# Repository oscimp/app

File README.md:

# app
OscillatorIMP ecosystem Linux applications

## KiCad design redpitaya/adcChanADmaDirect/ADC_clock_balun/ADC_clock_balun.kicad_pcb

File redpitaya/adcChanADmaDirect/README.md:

# Adc ChanA to CPU with DMA direct

## Purpose

This application is used to fetch, from ADC channelA, a large amount of sample.
By using the DMA to store data in CPU RAM instead of BRAM it's possible to
bypass the redpitaya Zynq resources limitation.

By default this project fetches 1Msamples 16bits at full speed (125MS/s)

To sample both ADC (instead of only ADC channelA), update the design with
```
NB_INPUT 2
```
The number of samples and connections will be updated automagically.

## Usage

After executing *adcChanADmaDirect_us* a binary file called *dump.bin* is
present in current directory. To read content using Gnu Octave in single channel mode:
```
fd = fopen("dump.bin"); dd = fread(fd, inf, "int16"); fclose(fd); 
```
and in dual channel mode
```
fd = fopen("dump.bin"); dd = fread(fd, inf, "int16"); fclose(fd); d1=dd(1:2:end); d2=dd(2:2:end);
```

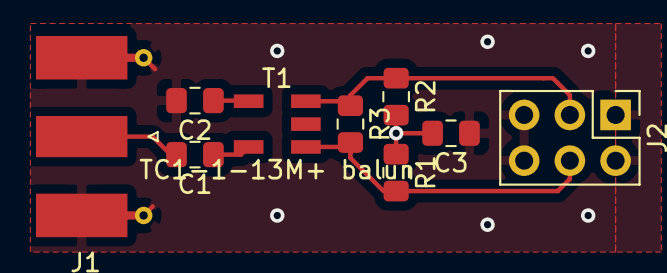
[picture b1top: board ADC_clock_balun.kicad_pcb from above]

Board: 2 copper layers, 9 parts (0 on the bottom side), 7 nets.

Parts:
C1, C2, C3: 100n; C_0805_2012Metric_Pad1.15x1.40mm_HandSolder
J1: Conn_Coaxial; SMA_Molex_73251-1153_EdgeMount_Horizontal
J2: Conn_02x03_Counter_Clockwise; PinHeader_2x03_P2.54mm_Vertical
R1, R2: 50; R_0805_2012Metric_Pad1.15x1.40mm_HandSolder
R3: 100; R_0805_2012Metric_Pad1.15x1.40mm_HandSolder
T1: TC1-1-13M+ balun; AT224-1A

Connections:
GND: C2.2, C3.1, J1.2, J2.1, J2.2, J2.5, J2.6
unnamed: C1.1, T1.4
unnamed: C1.2, J1.1
unnamed: C2.1, T1.6
unnamed: C3.2, R1.1, R2.2
unnamed: J2.3, R2.1, R3.1, T1.1
unnamed: J2.4, R1.2, R3.2, T1.3

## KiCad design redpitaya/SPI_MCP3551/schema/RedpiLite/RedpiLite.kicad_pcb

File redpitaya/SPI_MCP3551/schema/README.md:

Eagle 7 CAD electronics board schematic and layout, imported into KiCAD 7
and assigned layers (top, bottom and dimensions to F.Cu, B.Cu and Edge Cuts).

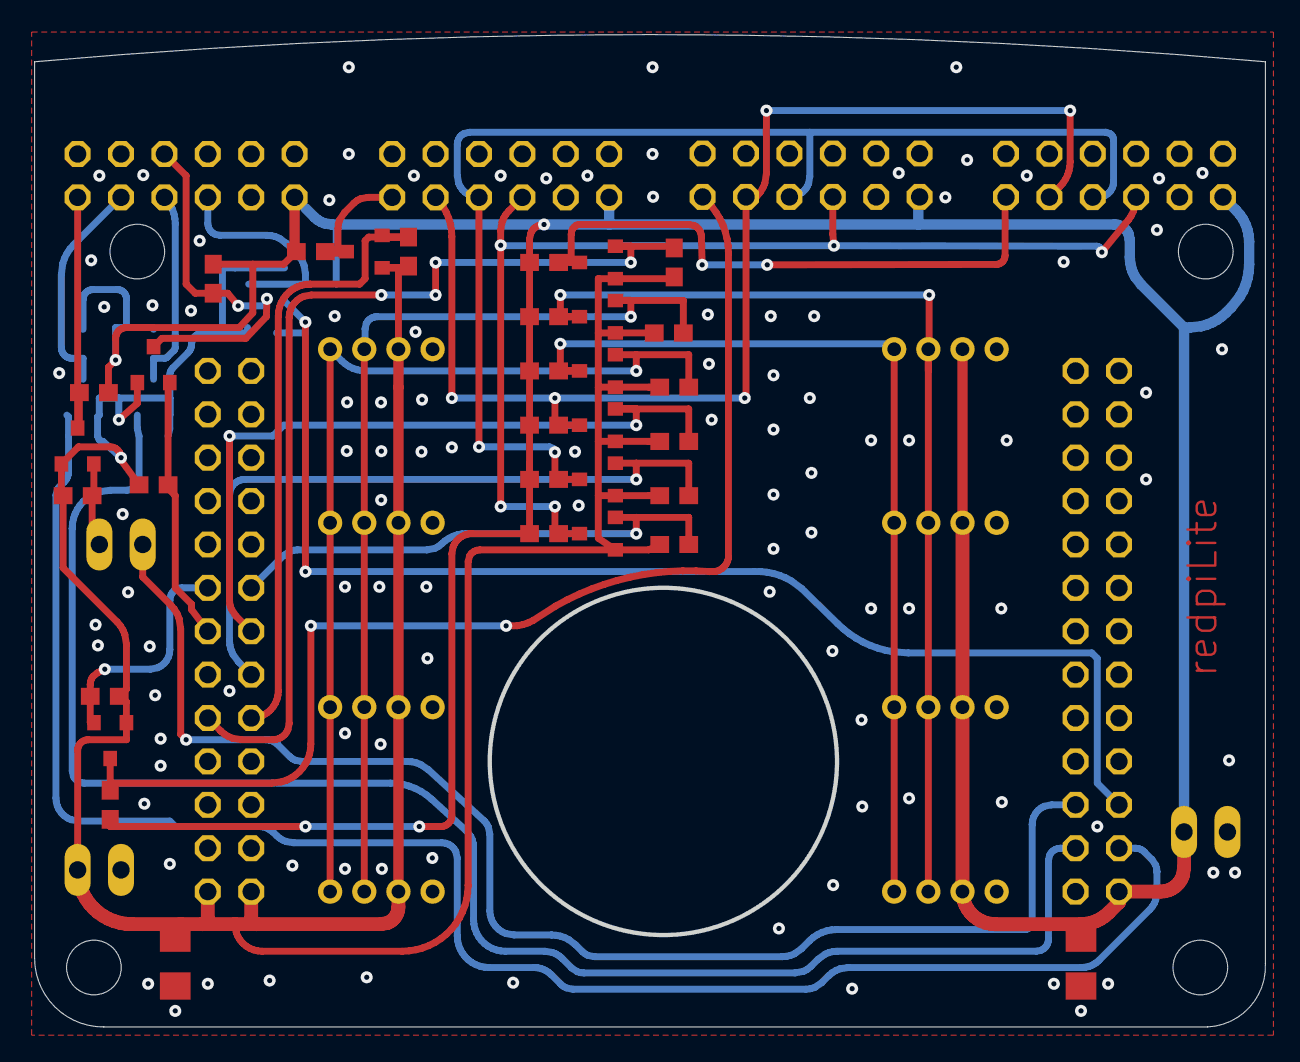
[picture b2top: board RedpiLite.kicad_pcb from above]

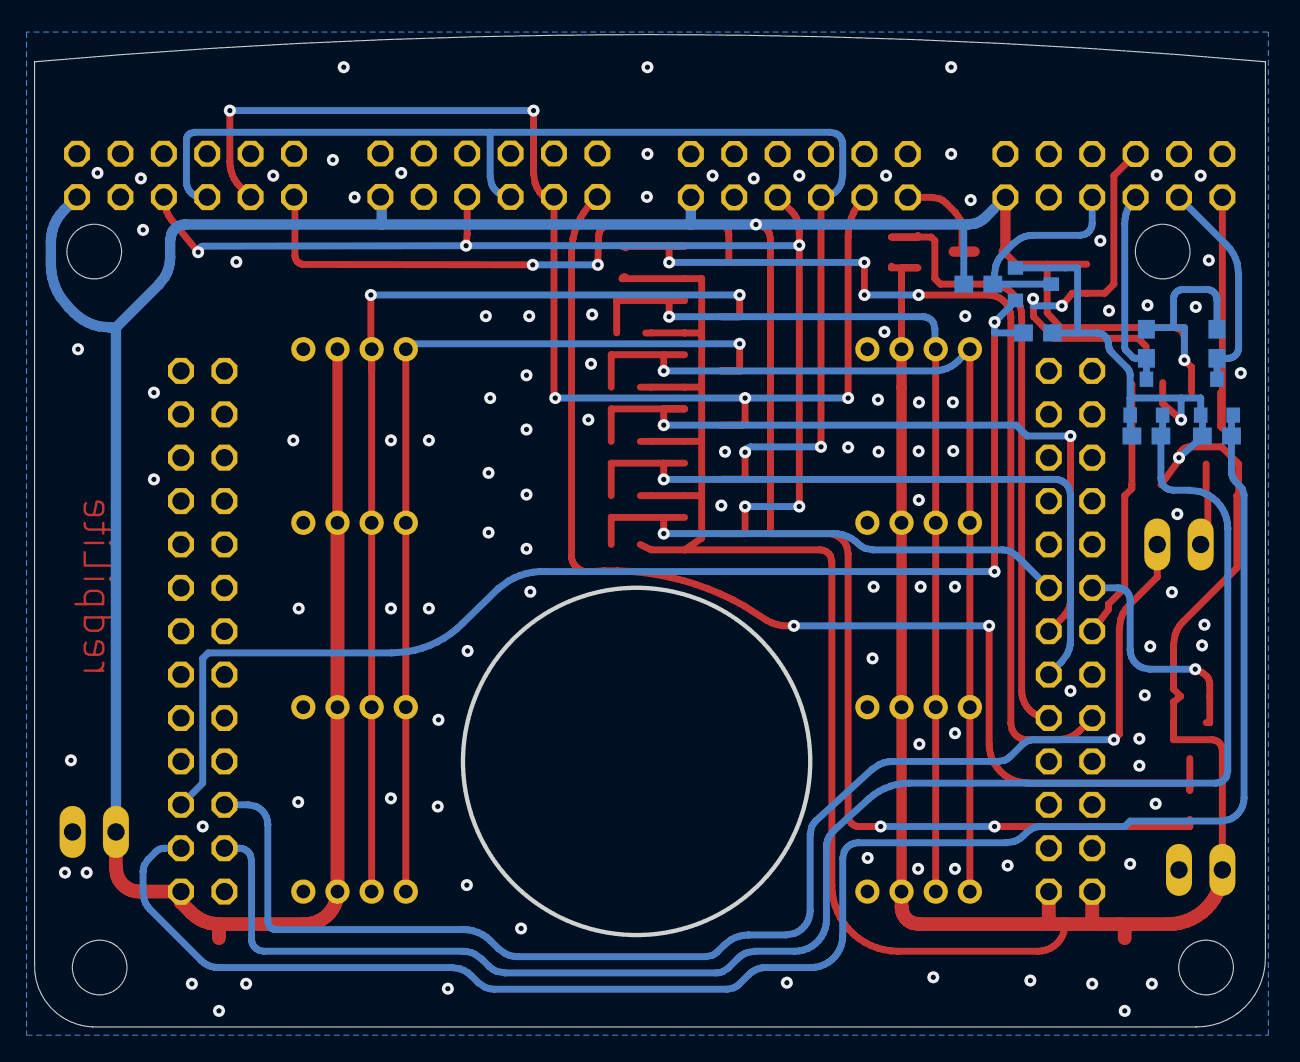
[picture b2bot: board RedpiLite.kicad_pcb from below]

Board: 2 copper layers, 71.8 x 57.9 mm, 62 parts (9 on the bottom side), 30 nets.

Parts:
+5V0: 1X02
@HOLE0, @HOLE1, @HOLE2, @HOLE3: (no value)
C1, C2: 4.7µF; C1206
E1, E2: 2X13
JUMP0: 1X02
P1, P2, P3, P4, P5, P6, P7, P8: JST-PH4
PMOD1, PMOD2, PMOD3, PMOD4: 2X06_90
R1, R2, R3, R4, R5, R6, R7, R8, R9, R10, R11, R12, R13, R14, R15, R16, R17, R18, R19, R20, R21, R22, R23, R24, R25, R26: 10K; 0603-RES
T1, T2, T3, T4, T5, T6, T7, T8, T9, T10, T11, T12, T13: BSS138; SOT23-3
UNK3V3: 1X02

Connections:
+3V3: C2.1, E1.1, E1.2, P1.3, P2.3, P3.3, P4.3, R1.1, R3.1, R5.1, R7.1, R9.1, R11.1, R13.1, R15.1, R17.1, R19.1, R21.1, R23.1, R25.1, T1.1, T2.1, T3.1, T4.1, T5.1, T6.1, T7.1, T8.1, T9.1, T10.1, T11.1, T12.1, T13.1, UNK3V3.1
+5V: +5V0.1, C1.1, E2.1, P5.3, P6.3, P7.3, P8.3, PMOD1.11, PMOD2.11, PMOD3.11, PMOD4.11, R2.1, R4.1, R6.1, R8.1, R10.1, R12.1, R14.1, R16.1, R18.1, R20.1, R22.1, R24.1, R26.1
CLK1: PMOD4.7, R20.2, T10.3
CLK2: PMOD1.7, PMOD2.7, PMOD3.7, R2.2, T1.3
CS1: PMOD1.1, R12.2, T6.3
CS2: PMOD2.1, R14.2, T7.3
CS3: PMOD3.1, R16.2, T8.3
CS4: PMOD4.1, R18.2, T9.3
CS#: E2.6, JUMP0.1
CS#': JUMP0.2, R17.2, T9.2
GND: +5V0.2, C1.2, C2.2, E1.19, E1.20, E1.25, E1.26, E2.12, E2.21, E2.22, E2.25, E2.26, P1.4, P2.4, P3.4, P4.4, P5.4, P6.4, P7.4, P8.4, PMOD1.9, PMOD2.9, PMOD3.9, PMOD4.9, UNK3V3.2
MISO: E2.4, R21.2, T11.2
MISO1: PMOD4.5, R22.2, T11.3
MISO2: PMOD1.5, PMOD2.5, PMOD3.5, R4.2, T2.3
MOSI: E2.3, R23.2, T12.2
MOSI1: PMOD4.3, R24.2, T12.3
MOSI2: PMOD1.3, PMOD2.3, PMOD3.3, R6.2, T3.3
PL_DIO3_N_CS1: E1.10, R11.2, T6.2
PL_DIO3_P_CS3: E1.9, R15.2, T8.2
PL_DIO4_P-MISO: E1.11, R3.2, T2.2
PL_DIO5_P-MOSI: E1.13, R5.2, T3.2
PL_DIO6_N_CS2: E1.16, R13.2, T7.2
PL_DIO6_P-CLK: E1.15, R1.2, T1.2
SCK: E2.5, R19.2, T10.2
SCL: P1.1, P2.1, P3.1, P4.1, R7.2, T4.2
SCL_5V: P5.1, P6.1, P7.1, P8.1, R8.2, T4.3
SDA: P1.2, P2.2, P3.2, P4.2, R9.2, T5.2
SDA_5V: P5.2, P6.2, P7.2, P8.2, R10.2, T5.3
SDSYNC: PMOD4.6, R26.2, T13.3
TEC_ON/OFF: E1.14, R25.2, T13.2

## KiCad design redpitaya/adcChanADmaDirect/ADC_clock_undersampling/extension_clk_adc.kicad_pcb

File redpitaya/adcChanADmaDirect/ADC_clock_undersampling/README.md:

Hardware modifications of the 14-bit Red Pitaya (also known as STEMlab 125-14) described
in report.pdf, and the associated KiCAD files (courtesy of Gilles Martin, FEMTO-ST, France)
for undersampling by getting rid of the unbalanced-balanced amplifier also acting as
low pass filter. Replacing the active amplifier with a broadband balun (tested over the
whole track-and-hold range up to 875 MHz input frequency) requires soldering three tiny
wires (differential pair + Vref) on each channel at your own risks after removing the
inductors connecting the differential amplifier output to the ADC inputs. The Vref signal
trace must be cut before soldering a wire to the via pad whose varnish will have been
removed with a sharp blade.

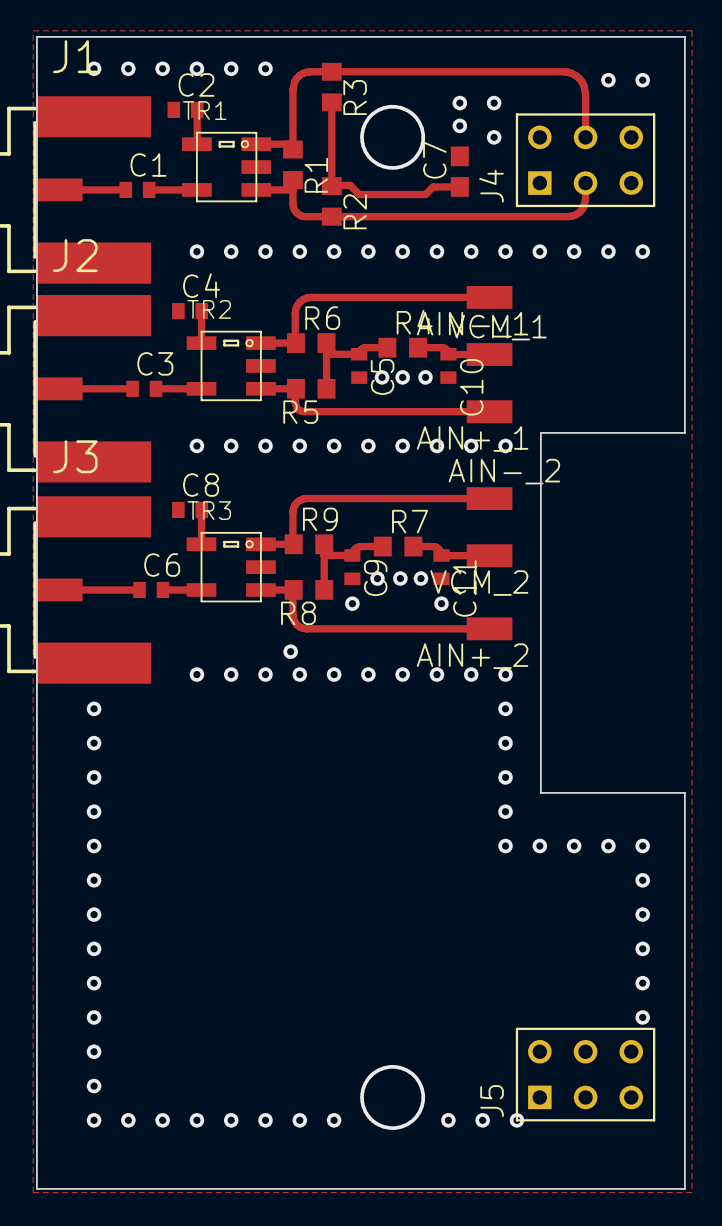
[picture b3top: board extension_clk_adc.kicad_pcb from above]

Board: 2 copper layers, 36.0 x 64.0 mm, 34 parts (0 on the bottom side), 21 nets.

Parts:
AIN+_1, AIN+_2: SMD2; SMD1,27-2,54
AIN-_1, AIN-_2: SMD2; SMD1,27-2,54
C1, C2, C3, C4, C5, C6, C8, C9, C10, C11: 100nF; C0402
C7: 100nF; C0603
J1, J2, J3: SMA_BORD
J4, J5: DBL_6; DBL6
R1: 100; R0603
R2, R3: 50; R0603
R4, R7: R-US_R0603; R0603
R5, R6, R8, R9: 25; R0603
TR1, TR2, TR3: TC1-1-13M; AT224-1A
VCM_1, VCM_2: SMD2; SMD1,27-2,54

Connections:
GND: C2.1, C4.1, C5.2, C7.2, C8.1, C9.2, C10.2, C11.2, J1.G@1, J1.G@2, J1.G@3, J1.G@4, J2.G@1, J2.G@2, J2.G@3, J2.G@4, J3.G@1, J3.G@2, J3.G@3, J3.G@4, J4.P$1, J4.P$2, J5.P$1, J5.P$2
unnamed: AIN+_1.1, R5.2, TR2.P$3
unnamed: AIN+_2.1, R8.2, TR3.P$3
unnamed: AIN-_1.1, R6.1, TR2.P$1
unnamed: AIN-_2.1, R9.1, TR3.P$1
unnamed: C1.1, J1.1
unnamed: C1.2, TR1.P$4
unnamed: C2.2, TR1.P$6
unnamed: C3.1, J2.1
unnamed: C3.2, TR2.P$4
unnamed: C4.2, TR2.P$6
unnamed: C5.1, R4.1, R5.1, R6.2
unnamed: C6.1, J3.1
unnamed: C6.2, TR3.P$4
unnamed: C7.1, R2.1, R3.2
unnamed: C8.2, TR3.P$6
unnamed: C9.1, R7.1, R8.1, R9.2
unnamed: C10.1, R4.2, VCM_1.1
unnamed: C11.1, R7.2, VCM_2.1
unnamed: J4.P$3, R1.2, R2.2, TR1.P$3
unnamed: J4.P$4, R1.1, R3.1, TR1.P$1

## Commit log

2018-11-11 add setenv.sh used to export corresponding env var
2018-12-06 Adds common Makefile for userspace applications. Used to compile application, convert dts to dtb, create the target directory and install all in this directory
2018-12-14 module_generator: A tool to creates the skeleton of an userspace application (Makefile, loader script and device-tree overlay).
2018-12-20 Makefile.inc: by default (without DONT_USE_LIB set in app Makefile) link to oscimp_fpga lib
2018-12-20 module_generator: avoid infinite loop in getNodes for recursive search
2018-12-20 add option(s) node(s) to add flags or others information to Makefile
2018-12-20 module_generator: update README about options node
2018-12-20 module_generator: supress vim temporary file
2019-02-01 Makefile: creates dest directories in two call
2019-02-13 module_generator: - XML structure change (see README for new structure based on root node named project). Conserve compatibility with original structure; - uses an XML in fpga_ip to obtain witch driv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
2019-02-14 ignore vim temporary files, dtb and binaries app
2019-03-07 Makefile.inc: add staging lib to LDFLAGS
2019-03-20 add USE_STATIC_LIB var to link application with liboscimp_fpga static version
2019-03-20 module_generator: remove overlay directory only if exist
2019-03-20 module_generator: add message when success
2019-03-20 module_generator: catching polymorphic type by value
2019-06-04 module_generator: add WA for pluto (different target phandle and no bitstream to flash at runtime)
2019-06-04 Makefile.inc: add rule to install app by ssh
2019-06-15 module_generator: fix warning
2019-06-18 plutosdr: add the default design but with modifications to use oscimpDigital ecosystem
2019-07-25 Makefile.inc: add env var to install extra files
2019-12-19 Pulsed RADAR SAW sensor reader: Redpitaya application
2019-12-19 Pulsed RADAR readme file: initial commit
2019-12-19 Update README.md
    bibliography
2019-12-19 Pulsed RADAR application README
2019-12-20 Update README.md
    Hardware setup
2019-12-20 Update README.md
    application
2019-12-20 E310 based optical probe (pictures)
2019-12-20 E310 based optical probe (tree structure)
2020-01-06 module_generator: backward compatibility in Makefile generation
2020-01-07 redpitaya:pulsed_radar: update README
2020-01-08 Makefile modification + add webserver_generator
2020-01-15 redpitaya: adcChanADmaDirect: dump 1MS 16bits full speed using dma direct IP
2020-01-24 e310:optical_probe: add design and application
2020-01-24 README.md file initial commit
2020-01-29 redpitaya:adcChanADmaDirect:app: add module list in Makefile
2020-01-29 redpitaya:adcChanADmaDirect:design: drop CANDR in connect_proc and cleanup
2020-01-30 tools:module_generator: add support for intel FPGA
2020-02-16 Create README.md
    app directory README description
2020-02-16 Update README.md
    README: full sentence
2020-02-27 external ADC clocking circuit with balun
2020-03-20 massive add lock design
2020-03-20 initial README
2020-04-09 missing fir* files
2020-05-09 README.md of webserver_generator
2020-05-11 Makefile.inc: don't try to compile/install binary application when no .c file is provided
2020-09-27 include the converters for redpitaya12 SignalLab in webserver_generator
2020-09-27 add redpitaya12 adc2dac example
2020-09-28 webserver_generator update
2020-10-02 remove unnecessary files
2020-10-02 add description of adc2dac example
2020-10-02 force markdown interp
2020-10-07 corrections in webserver_generator
2020-10-08 +f0 correction in webserver_generator
2020-10-09 example design double_iq_pid_vco for redpitaya12
2020-10-19 Buttons for redpidaya_converters_12 commutators in webserver_generator
2020-10-20 check ref clock status for redpitaya_converters_12 : webserver_generator
2020-10-20 fix load of redpitaya_converters_12 param in webserver_generator
2020-10-20 webserver_generator small errors correction
2020-10-27 bad /dev for ext ref status in webserver_generator
2021-01-06 undersampling
2021-01-11 redpitaya/adcChanADmaDirect: add redpitaya16 support
2021-01-11 correction in TCL script: 2 channel connections :)
2021-01-11 README: update num channels
2021-01-19 redpitaya/double_iq_pid_vco: redpitaya16 compatibility: WIP
2021-01-19 ignore log and jou files
2021-01-27 redpitaya/double_iq_pid_vco: introduce var for size after fir
2021-01-27 redpitaya/double_iq_pid_vco: fix typo
2021-01-28 double_iq_pid_vco diagram
2021-01-28 Update README.md
    zlib dependency
2021-01-29 update web server according to library updates
2021-01-29 screenshot
2021-01-29 replace string with boolean, slider callback function with onchange.do, remove UTF8 encoding
2021-01-30 webserver_generator for remi update
2021-02-04 app/tools/module_generator/DTSGenerator: add more check
2021-02-18 correct UTF-8 (remove) encoding
2021-03-09 pidv3 setpoint is working now
2021-03-16 tools/module_generator: suppress noisy address-cells and size-cells to the fragment level
2021-03-24 webserver_generator switchReal fix
2021-04-12 tools/webserver_generator: add missing shifterComplex_dyn
2021-04-14 tools/webserver_generator: fix chmod right, fix listener with recent remi
2021-05-19 delayTempoReal_axi in webserver_generator
2021-06-11 autorun_generator -> be lazy + webserver_generator switchComplex
2021-06-11 add autorun_generator readme
2021-07-15 Makefile.inc: fix sh script name
2021-07-16 minor correction in autorun_generator
2021-07-16 update readme autorun_generator
2021-07-20 redpitaya/double_iq_pid_vco: fix webserver types
2021-07-20 webserver regeneration procedure
2021-07-21 tools/webserver_generator: fix onchange/onclick. To revert with remi 2021.3.2
2021-07-21 tools/webserver_generator: set samp_rate according to the target board
2021-07-26 nco in webserver_fenerator: fix float load error
2021-08-24 tools/webserver_generator: force python3
2021-10-12 initial commit of phaselock1CH
2021-11-19 update double_iq_pid_vco
2022-04-01 first release of comb_lock application, version 0.10
2022-04-22 hardware modification to the 14-bit redpitaya for undersampling
2022-04-22 clean backup file
2022-04-22 directory description
2022-05-05 fix driver makefile name
2022-05-05 add partial pluto support; fix remi check boxes issues
2022-05-05 make compatible with v1.1 and 2k versions of remi
2022-05-05 switch: default to False (as IP)
2022-05-12 fix nco step, add addConst size and pid_coeff_size
2022-05-20 fix f-string
2023-09-05 SPI_MCP3551 and PMOD through FPGA
2023-09-05 comment from Gwen about dts error with voltage regulator description
2023-11-14 corrected delay ip control in webserver_generator.py
2024-03-09 redpitaya125-14: design example for the dataComplex2ram and dataComplex2ram_pingpong
2024-11-25 README app data2ram
2024-11-25 rename data2ram exampe
2024-11-30 redpitaya: dataReal2ram_pingpong example
2025-03-19 fix remi update
2025-06-10 redpitaya12: add double_dds example
2025-06-13 README
2025-06-13 webserver_generator: modify GPIO from pre-6 to post-6 kernel numbering
2025-06-13 update ListView callback API
2025-06-13 double_dds: complement README
2025-06-13 update app
2025-06-16 screenshots double_iq_pid_vco
2025-12-02 tinyxml version
